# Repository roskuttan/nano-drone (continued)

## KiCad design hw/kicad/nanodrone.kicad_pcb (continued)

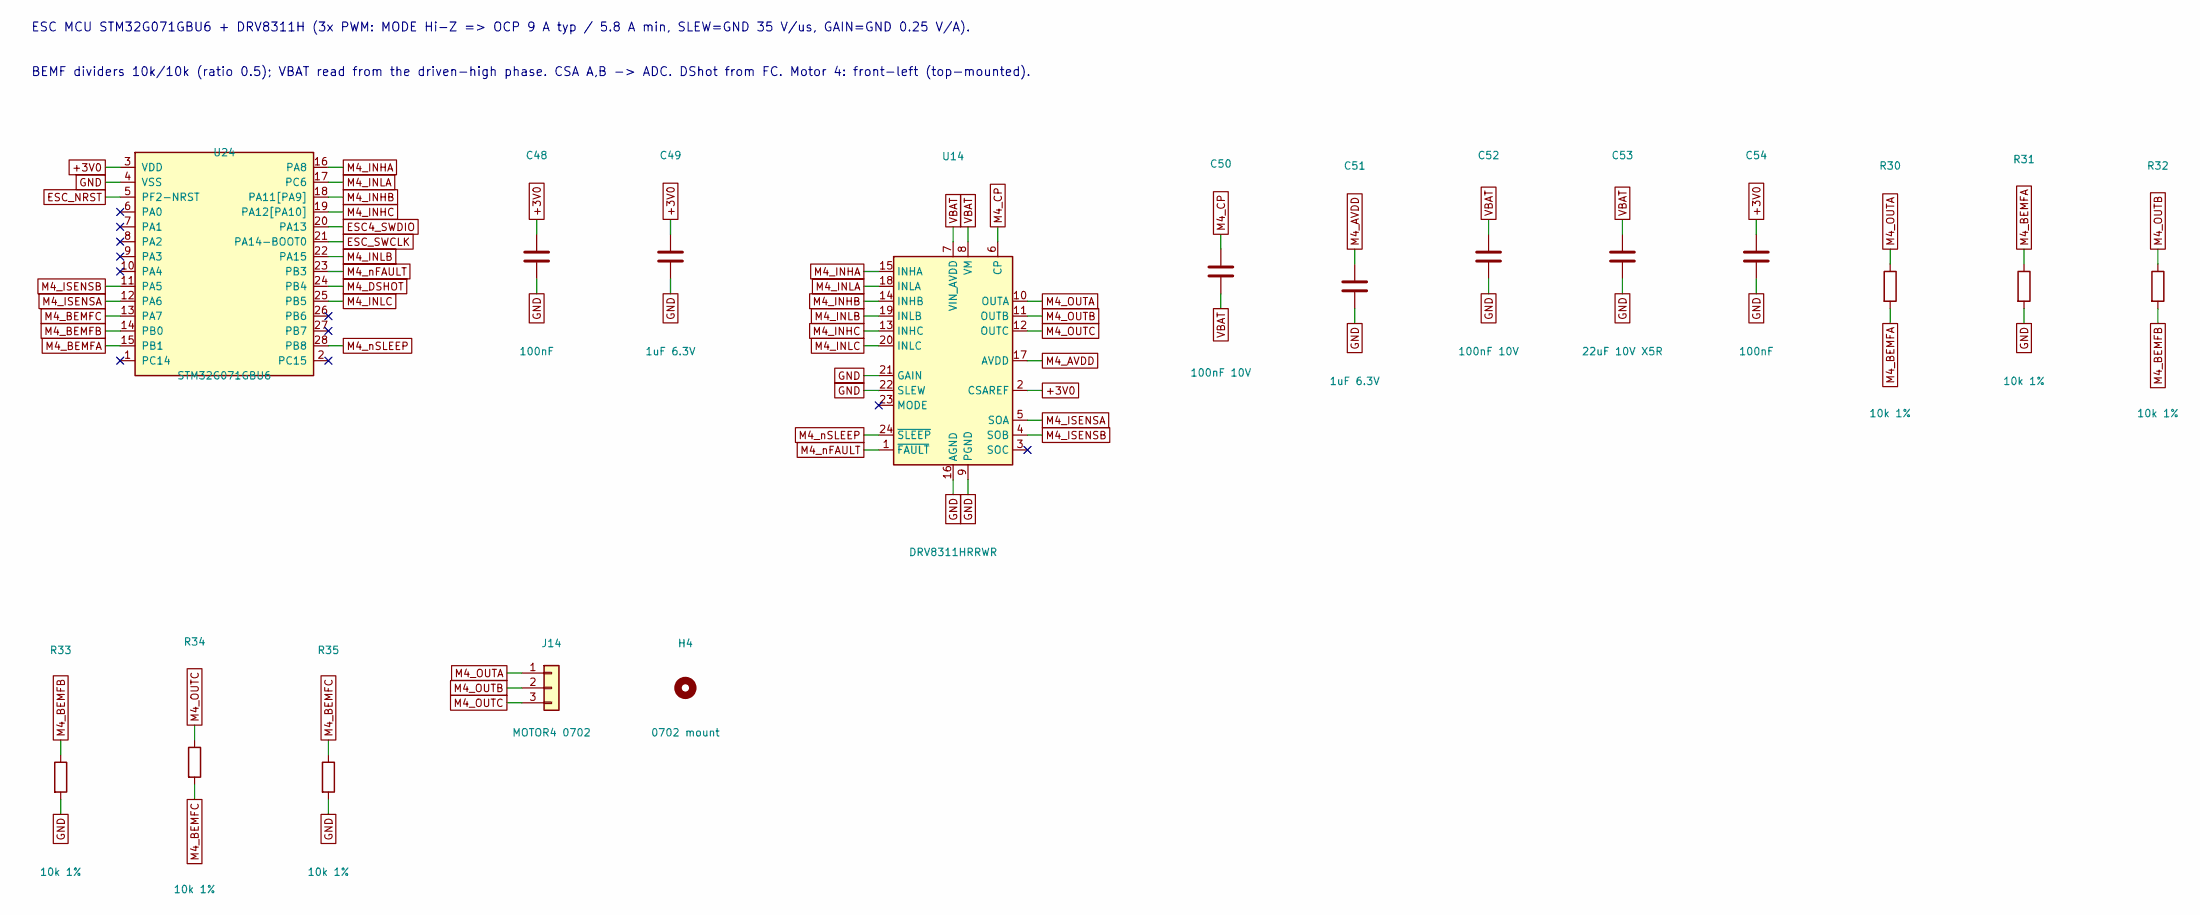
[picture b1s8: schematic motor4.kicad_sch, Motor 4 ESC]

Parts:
C48, C54: 100nF; C_0201_0603Metric
C49, C51: 1uF 6.3V; C_0201_0603Metric
C50, C52: 100nF 10V; C_0201_0603Metric
C53: 22uF 10V X5R; C_0603_1608Metric
H4: 0702 mount; Motor_0702_Mount
J14: MOTOR4 0702; MotorPads_3x_PTH
R30, R31, R32, R33, R34, R35: 10k 1%; R_0201_0603Metric
U14: DRV8311HRRWR; Texas_RRW0024A_WQFN-24-1EP_3x3mm_P0.4mm_EP1.9x1.9mm_Thermal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; MPN DRV8311HRRWR; LCSC C5218862
U24: STM32G071GBU6; QFN-28_4x4mm_P0.5mm; MPN STM32G071GBU6; LCSC C529347

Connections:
+3V0: C48.1, C49.1, C54.1, U14.2 (CSAREF), U24.3 (VDD); also elsewhere on the board
ESC4_SWDIO: U24.20 (PA13); also elsewhere on the board
ESC_NRST: U24.5 (PF2-NRST); also elsewhere on the board
ESC_SWCLK: U24.21 (PA14-BOOT0); also elsewhere on the board
GND: C48.2, C49.2, C51.2, C52.2, C53.2, C54.2, R31.2, R33.2, R35.2, U14.9 (PGND), U14.16 (AGND), U14.21 (GAIN), U14.22 (SLEW), U14.25 (PGND), U24.4 (VSS); also elsewhere on the board
M4_AVDD: C51.1, U14.17 (AVDD)
M4_BEMFA: R30.2, R31.1, U24.15 (PB1)
M4_BEMFB: R32.2, R33.1, U24.14 (PB0)
M4_BEMFC: R34.2, R35.1, U24.13 (PA7)
M4_CP: C50.1, U14.6 (CP)
M4_DSHOT: U24.24 (PB4); also elsewhere on the board
M4_INHA: U14.15 (INHA), U24.16 (PA8)
M4_INHB: U14.14 (INHB), U24.18 (PA11[PA9])
M4_INHC: U14.13 (INHC), U24.19 (PA12[PA10])
M4_INLA: U14.18 (INLA), U24.17 (PC6)
M4_INLB: U14.19 (INLB), U24.22 (PA15)
M4_INLC: U14.20 (INLC), U24.25 (PB5)
M4_ISENSA: U14.5 (SOA), U24.12 (PA6)
M4_ISENSB: U14.4 (SOB), U24.11 (PA5)
M4_OUTA: J14.1, R30.1, U14.10 (OUTA)
M4_OUTB: J14.2, R32.1, U14.11 (OUTB)
M4_OUTC: J14.3, R34.1, U14.12 (OUTC)
M4_nFAULT: U14.1 (~FAULT), U24.23 (PB3)
M4_nSLEEP: U14.24 (~SLEEP), U24.28 (PB8)
VBAT: C50.2, C52.1, C53.1, U14.7 (VIN_AVDD), U14.8 (VM); also elsewhere on the board

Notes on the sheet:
ESC MCU STM32G071GBU6 + DRV8311H (3x PWM: MODE Hi-Z => OCP 9 A typ / 5.8 A min, SLEW=GND 35 V/us, GAIN=GND 0.25 V/A).
BEMF dividers 10k/10k (ratio 0.5); VBAT read from the driven-high phase. CSA A,B -> ADC. DShot from FC. Motor 4: front-left (top-mounted).

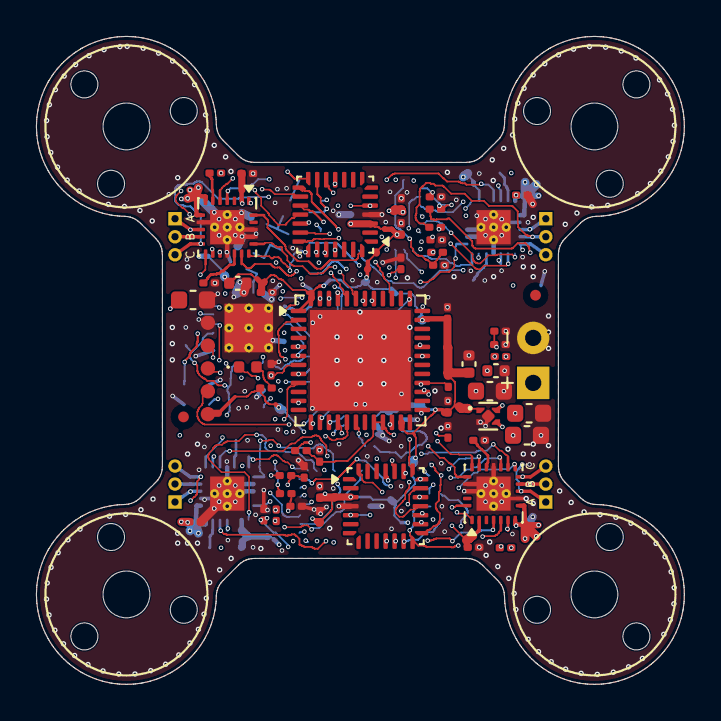
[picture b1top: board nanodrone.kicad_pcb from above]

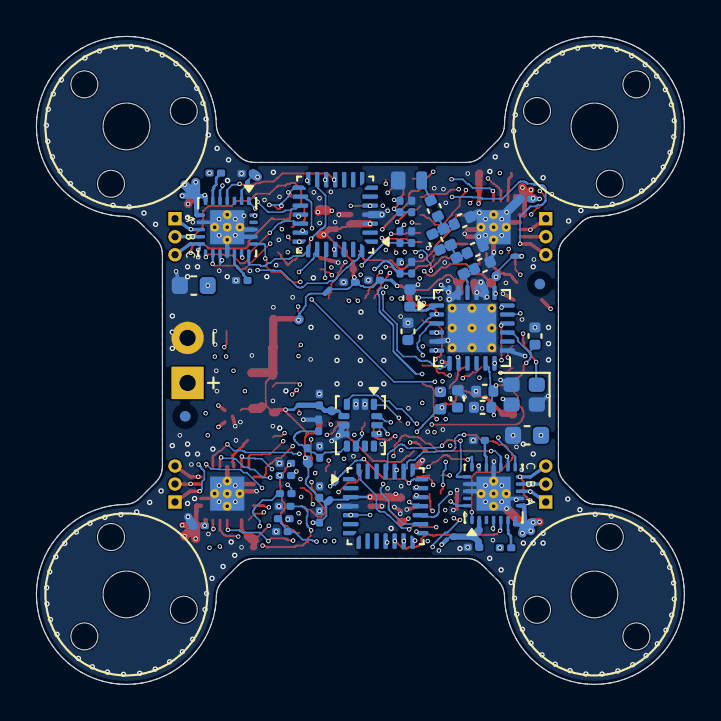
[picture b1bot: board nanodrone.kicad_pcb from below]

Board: 6 copper layers, 36.0 x 36.0 mm, 117 parts (56 on the bottom side), 116 nets.

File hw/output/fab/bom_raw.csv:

"Ref","Value","Footprint","Qty","LCSC","MPN"
"C1,C2,C32,C39,C46,C53","22uF 10V X5R","Capacitor_SMD:C_0603_1608Metric","6","",""
"C3","1uF 10V","Capacitor_SMD:C_0402_1005Metric","1","",""
"C4","2.2uF 6.3V","Capacitor_SMD:C_0402_1005Metric","1","",""
"C5,C6,C7,C8,C11,C12,C14,C15,C27,C33,C34,C40,C41,C47,C48,C54","100nF","Capacitor_SMD:C_0201_0603Metric","16","",""
"C9,C18","4.7uF 6.3V","Capacitor_SMD:C_0402_1005Metric","2","",""
"C10,C13,C28,C30,C35,C37,C42,C44,C49,C51","1uF 6.3V","Capacitor_SMD:C_0201_0603Metric","10","",""
"C16,C17","100nF","Capacitor_SMD:C_0402_1005Metric","2","",""
"C19,C20","10nF","Capacitor_SMD:C_0402_1005Metric","2","",""
"C21","470nF","Capacitor_SMD:C_0402_1005Metric","1","",""
"C22","0.8pF C0G","Capacitor_SMD:C_0402_1005Metric","1","",""
"C23,C25","1.2pF C0G","Capacitor_SMD:C_0402_1005Metric","2","",""
"C24","0.5pF C0G","Capacitor_SMD:C_0402_1005Metric","1","",""
"C26","100pF C0G","Capacitor_SMD:C_0402_1005Metric","1","",""
"C29,C31,C36,C38,C43,C45,C50,C52","100nF 10V","Capacitor_SMD:C_0201_0603Metric","8","",""
"D1","RED","LED_SMD:LED_0402_1005Metric","1","",""
"FB1","600R@100MHz","Inductor_SMD:L_0402_1005Metric","1","",""
"J1","BATTERY 1S","nanodrone:BatteryPads_PTH","1","",""
"J2","ANTENNA 50R","nanodrone:AntennaPads_SMD","1","",""
"J3","SWD","nanodrone:SWD_Pads_1x05_P1.27mm","1","",""
"J11","MOTOR1 0702","nanodrone:MotorPads_3x_PTH","1","",""
"J12","MOTOR2 0702","nanodrone:MotorPads_3x_PTH","1","",""
"J13","MOTOR3 0702","nanodrone:MotorPads_3x_PTH","1","",""
"J14","MOTOR4 0702","nanodrone:MotorPads_3x_PTH","1","",""
"L1","3.0nH","Inductor_SMD:L_0402_1005Metric","1","",""
"L2","2.5nH","Inductor_SMD:L_0402_1005Metric","1","",""
"R1,R2,R9,R10,R11,R12,R13,R14,R16,R17,R18,R19,R20,R21,R23,R24,R25,R26,R27,R28,R30,R31,R32,R33,R34,R35","10k 1%","Resistor_SMD:R_0201_0603Metric","26","",""
"R3,R7","10R","Resistor_SMD:R_0201_0603Metric","2","",""
"R4,R5","10k","Resistor_SMD:R_0201_0603Metric","2","",""
"R6","1k","Resistor_SMD:R_0201_0603Metric","1","",""
"U1","TPS7A2030PDQNR","Package_SON:Texas_X2SON-4_1x1mm_P0.65mm","1","","TPS7A2030PDQNR"
"U2","STM32G431CBU6","Package_DFN_QFN:QFN-48-1EP_7x7mm_P0.5mm_EP5.6x5.6mm","1","C529356","STM32G431CBU6"
"U3","LSM6DSV16XTR","Package_LGA:LGA-14_3x2.5mm_P0.5mm_LayoutBorder3x4y","1","C5267406","LSM6DSV16XTR"
"U4","SX1280IMLTRT","Package_DFN_QFN:QFN-24-1EP_4x4mm_P0.5mm_EP2.7x2.7mm_ThermalVias","1","C125969","SX1280IMLTRT"
"U11,U12,U13,U14","DRV8311HRRWR","Package_DFN_QFN:Texas_RRW0024A_WQFN-24-1EP_3x3mm_P0.4mm_EP1.9x1.9mm_ThermalVias","4","C5218862","DRV8311HRRWR"
"U21,U22,U23,U24","STM32G071GBU6","Package_DFN_QFN:QFN-28_4x4mm_P0.5mm","4","C529347","STM32G071GBU6"
"Y1","52MHz 10pF 10ppm","Crystal:Crystal_SMD_2016-4Pin_2.0x1.6mm","1","",""

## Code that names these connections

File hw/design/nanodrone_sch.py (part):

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TP = "TestPoint:TestPoint_Pad_D1.0mm"
# rev B option: per-ESC SWD pogo pads instead of the FC's SWD programming bus (NANODRONE_ESC_TP=1)
ESC_TP = os.environ.get("NANODRONE_ESC_TP") == "1"
# rev C option (NANODRONE_NFAULT_PU=0): no external 10k nFAULT pull-ups; the ESC MCU's PB3 internal pull-up does it
NFAULT_PU = os.environ.get("NANODRONE_NFAULT_PU", "0") == "1"   # rev C default: no external pull-ups
FP_ESC_SWD = "nanodrone:SWD_Pads_1x03_P1.0mm"
FP_DRV = "Package_DFN_QFN:Texas_RRW0024A_WQFN-24-1EP_3x3mm_P0.4mm_EP1.9x1.9mm_ThermalVias"
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    # Layout rev B pin swap (routability): every pin that leaves the package does so on the side that faces its
    # destination. Package sides: W = pins 1-12 (N->S), S = 13-24 (W->E), E = 25-36 (S->N), N = 37-48 (E->W).
    "1": "+3V0",                      # VBAT (no backup battery)
    "2": "LED_K",                     # PC13 sinks the status LED (<=3 mA)
    "5": "ESC4_SWDIO",                # PF0 (HSE unused: GPIO), W side towards ESC4 (north-west)
    "6": "RF_NRESET",                 # PF1, W side towards the radio
    "7": "NRST",                      # PG10-NRST
    # DShot on TIM2_CH1..CH4 (one timer, DMA, bidirectional capture), each channel on the side of its ESC
    "8": "M4_DSHOT", "9": "M3_DSHOT",                                      # PA0 TIM2_CH1, PA1 TIM2_CH2 (W)
    "31": "M1_DSHOT", "32": "M2_DSHOT",                                    # PA9 TIM2_CH3, PA10 TIM2_CH4 (E)
    "11": "ESC3_SWDIO",               # PA3, W side towards ESC3 (south-west)
    "25": "VBAT_SENSE",               # PB12 ADC1_IN11, E side towards the divider
    "13": "IMU_SCK", "14": "IMU_MISO", "15": "IMU_MOSI",                   # SPI1 PA5/PA6/PA7
    "16": "IMU_CS", "17": "IMU_INT1", "18": "IMU_INT2",                    # PC4, PB0, PB1
    "20": "+3V0A", "21": "+3V0A",     # VREF+, VDDA (via ferrite)
    "22": "ESC1_SWDIO",               # PB10, S side towards ESC1 (south-east)
    "39": "ESC2_SWDIO",               # PC10, N side towards ESC2 (north-east)
    "27": "ESC_SWCLK", "28": "ESC_NRST",                                   # PB14, PB15 (open-drain)
    "23": "+3V0", "35": "+3V0", "48": "+3V0", "49": "GND",
    "36": "SWDIO", "37": "SWCLK",     # PA13, PA14
    "41": "RF_SCK", "42": "RF_MISO", "43": "RF_MOSI",                      # SPI3 PB3/PB4/PB5
    "44": "RF_NSS", "45": "RF_BUSY", "46": "BOOT0", "47": "RF_DIO1",       # PB6, PB7, PB8-BOOT0, PB9
}
if ESC_TP:      # no SWD bus to the ESCs: PF0, PA3, PB10, PC10, PB14, PB15 stay free
    for _pin in ("5", "11", "22", "39", "27", "28"):
        FC_PINS.pop(_pin)

G071_PINS = [   # (pin, name, type, side) - STM32G071GBU6 UFQFPN28 (DS12232 / ST open pin data)
    ("3", "VDD", "power_in", "L"), ("4", "VSS", "power_in", "L"), ("5", "PF2-NRST", "bidirectional", "L"),
    ("6", "PA0", "bidirectional", "L"), ("7", "PA1", "bidirectional", "L"), ("8", "PA2", "bidirectional", "L"),
    ("9", "PA3", "bidirectional", "L"), ("10", "PA4", "bidirectional", "L"), ("11", "PA5", "bidirectional", "L"),
    ("12", "PA6", "bidirectional", "L"), ("13", "PA7", "bidirectional", "L"), ("14", "PB0", "bidirectional", "L"),
    ("15", "PB1", "bidirectional", "L"), ("1", "PC14", "bidirectional", "L"),
    ("16", "PA8", "bidirectional", "R"), ("17", "PC6", "bidirectional", "R"),
    ("18", "PA11[PA9]", "bidirectional", "R"), ("19", "PA12[PA10]", "bidirectional", "R"),
    ("20", "PA13", "bidirectional", "R"), ("21", "PA14-BOOT0", "bidirectional", "R"),
    ("22", "PA15", "bidirectional", "R"), ("23", "PB3", "bidirectional", "R"), ("24", "PB4", "bidirectional", "R"),
    ("25", "PB5", "bidirectional", "R"), ("26", "PB6", "bidirectional", "R"), ("27", "PB7", "bidirectional", "R"),
    ("28", "PB8", "bidirectional", "R"), ("2", "PC15", "bidirectional", "R"),
]
G071 = K.make_symbol("STM32G071GBU6", G071_PINS, ref="U", footprint=FP_ESC,
                     datasheet="https://www.st.com/resource/en/datasheet/stm32g071gb.pdf",
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    pins = {   # STM32G071GBU6 pin -> net (per motor ESC)
        "3": "+3V0", "4": "GND", "5": "ESC_NRST",
        # BEMF + CSA inputs on the ADC pins of the package corner that faces the driver (routability: the old
        # PA0-PA2 sat on the far edge, over the neighbouring ESC MCU on the other side). Zero-cross detection
        # is ADC-based (2.5 Msps); none of these pins is a comparator input.
        "15": p + "BEMFA", "14": p + "BEMFB", "13": p + "BEMFC",   # PB1 ADC1_IN9, PB0 ADC1_IN8, PA7 ADC1_IN7
        "12": p + "ISENSA", "11": p + "ISENSB",                    # PA6 ADC1_IN6, PA5 ADC1_IN5
        "16": p + "INHA", "18": p + "INHB", "19": p + "INHC",      # TIM1_CH1 PA8, TIM1_CH2 PA9*, TIM1_CH3 PA10*
        "17": p + "INLA", "22": p + "INLB", "25": p + "INLC",      # PC6, PA15, PB5
        "24": p + "DSHOT",                                         # PB4 TIM3_CH1 (DMA, bidirectional DShot)
        "28": p + "nSLEEP", "23": p + "nFAULT",                    # PB8 out, PB3 in (corner next to the driver)
        "20": "ESC%d_SWDIO" % m, "21": "ESC_SWCLK",                # PA13, PA14 (SWD from the FC)
    }   # * pins 18/19 = PA9/PA10 after SYSCFG PA11/PA12 remap
    if ESC_TP:
        # rev B: no SWD bus from the FC (its six board-spanning nets were the routing bottleneck). Each ESC has
        # its own pogo pads for the one-time bootloader flash; updates then go over the DShot wire.
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    "STM32G431CBU6 UFQFPN48: SPI1 -> IMU, SPI3 -> SX1280, TIM2 CH1-4 -> bidirectional DShot to the 4 ESCs.",
    ("The ESC MCUs have their own SWD pogo pads (one-time bootloader flash); firmware updates go over DShot."
     if ESC_TP else
     "PB10/PC10/PA3/PF0 + PB14/PB15 form an SWD programming bus to the ESC MCUs (own SWDIO each, shared SWCLK "
     "+ NRST)."),
])
mcu.add(K.Part("U2", "MCU_ST_STM32G4:STM32G431CBUx", FC_PINS, value="STM32G431CBU6", footprint=FP_FC,
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    if NFAULT_PU:
        R(s, p + "nFAULT", "+3V0", "10k")                   # nFAULT open-drain pull-up
    else:
        ref("R")                                            # rev C: PB3 internal pull-up; later refs keep numbers
    C(s, p + "CP", "VBAT", "100nF 10V")                     # CCP between CP and VM
    C(s, p + "AVDD", "GND", "1uF 6.3V")                     # CAVDD 0.7..7 uF
    C(s, "VBAT", "GND", "100nF 10V")                        # CVM1 / CVIN_AVDD1 (pins 7,8 adjacent)
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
